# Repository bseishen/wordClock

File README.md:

wordClock
==========

This repository contains my own take on the word clock. Insperation came from an instructable(http://www.instructables.com/id/Sleek-word-clock/). The hardware drives a matrix of 13x8 led's. Uses mosfets for the rows and a TLC5940 for the column driver.

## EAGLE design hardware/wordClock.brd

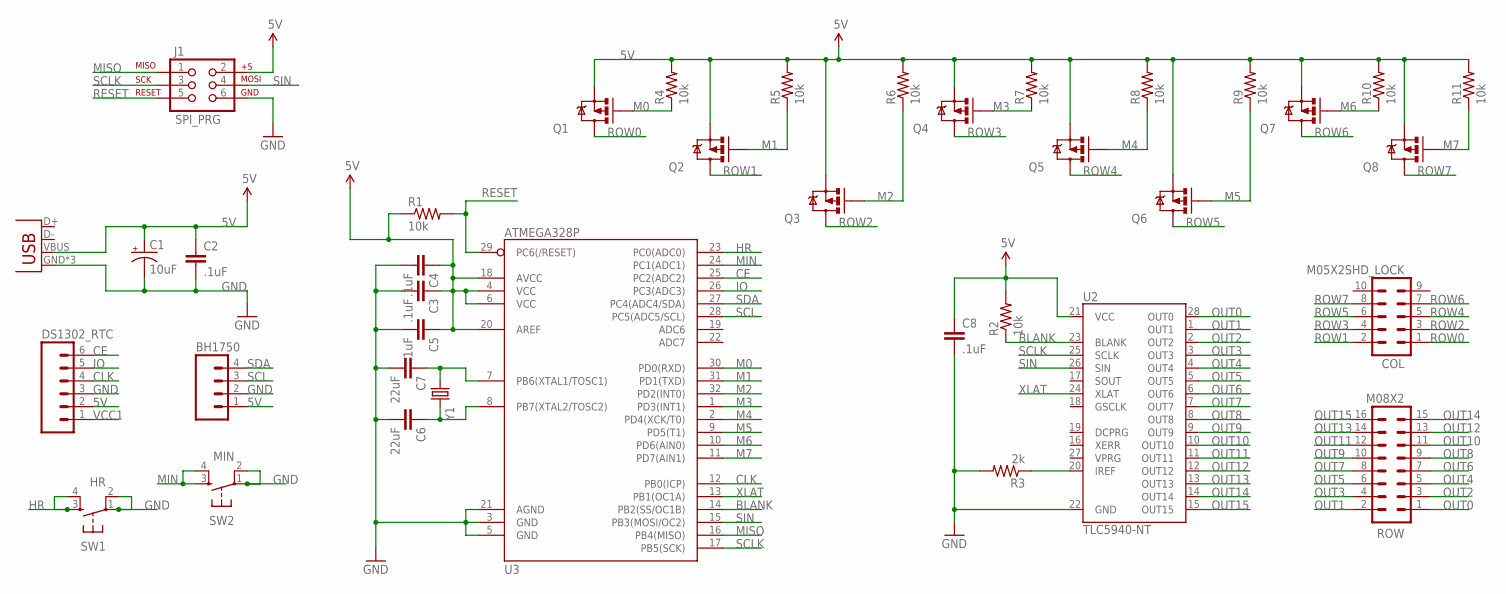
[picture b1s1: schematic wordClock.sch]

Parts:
BH1750: M04LOCK; 1X04_LOCK
C1: 10uF; PANASONIC_D
C2, C3, C4, C5, C8: .1uF; 0805
C6, C7: 22uF; 0805
COL: M05X2SHD_LOCK; 2X5-SHROUDED_LOCK
DS1302_RTC: M06FEMALE_LOCK; 1X06_FEMALE_LOCK.010
J1: SPI_PRG; 2X3_LOCK
JP1: USB-MICROB
Q1, Q2, Q3, Q4, Q5, Q6, Q7, Q8: MOSFET-PCHANNELSMD; SOT23-3
R1, R2, R4, R5, R6, R7, R8, R9, R10, R11: 10k; 0805
R3: 2k; 0805
ROW: M08X2; 2X8
SW1: HR; TACTILE-PTH
SW2: MIN; TACTILE-PTH
U2: TLC5940-NT; DIL28-3
U3: ATMEGA328P; TQFP32-08
Y1: CRYSTALHC49UV; HC49U-V

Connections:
5V: BH1750.1, C1.+, C2.1, C3.1, C4.1, C5.1, C8.1, DS1302_RTC.2, J1.2, JP1.VBUS, Q1.2 (S), Q2.2 (S), Q3.2 (S), Q4.2 (S), Q5.2 (S), Q6.2 (S), Q7.2 (S), Q8.2 (S), R1.1, R2.2, R4.2, R5.2, R6.2, R7.2, R8.2, R9.2, R10.2, R11.2, U2.21 (VCC), U3.4 (VCC), U3.6 (VCC), U3.18 (AVCC), U3.20 (AREF)
BLANK: R2.1, U2.23 (BLANK), U3.14 (PB2(SS/OC1B))
CE: DS1302_RTC.6, U3.25 (PC2(ADC2))
CLK: DS1302_RTC.4, U3.12 (PB0(ICP))
GND: BH1750.2, C1.-, C2.2, C3.2, C4.2, C5.2, C6.2, C7.2, C8.2, DS1302_RTC.3, J1.6, JP1.GND, JP1.MT1 (GND), JP1.MT2 (GND), R3.2, SW1.1, SW1.2, SW2.1, SW2.2, U2.22 (GND), U3.3 (GND), U3.5 (GND), U3.21 (AGND)
HR: SW1.3, SW1.4, U3.23 (PC0(ADC0))
IO: DS1302_RTC.5, U3.26 (PC3(ADC3))
M0: Q1.1 (G), R4.1, U3.30 (PD0(RXD))
M1: Q2.1 (G), R5.1, U3.31 (PD1(TXD))
M2: Q3.1 (G), R6.1, U3.32 (PD2(INT0))
M3: Q4.1 (G), R7.1, U3.1 (PD3(INT1))
M4: Q5.1 (G), R8.1, U3.2 (PD4(XCK/T0))
M5: Q6.1 (G), R9.1, U3.9 (PD5(T1))
M6: Q7.1 (G), R10.1, U3.10 (PD6(AIN0))
M7: Q8.1 (G), R11.1, U3.11 (PD7(AIN1))
MIN: SW2.3, SW2.4, U3.24 (PC1(ADC1))
MISO: J1.1, U3.16 (PB4(MISO))
unnamed: R3.1, U2.20 (IREF)
unnamed: C6.1, U3.8 (PB7(XTAL2/TOSC2)), Y1.2
unnamed: C7.1, U3.7 (PB6(XTAL1/TOSC1)), Y1.1
OUT0: ROW.1, U2.28 (OUT0)
OUT1: ROW.2, U2.1 (OUT1)
OUT2: ROW.3, U2.2 (OUT2)
OUT3: ROW.4, U2.3 (OUT3)
OUT4: ROW.5, U2.4 (OUT4)
OUT5: ROW.6, U2.5 (OUT5)
OUT6: ROW.7, U2.6 (OUT6)
OUT7: ROW.8, U2.7 (OUT7)
OUT8: ROW.9, U2.8 (OUT8)
OUT9: ROW.10, U2.9 (OUT9)
OUT10: ROW.11, U2.10 (OUT10)
OUT11: ROW.12, U2.11 (OUT11)
OUT12: ROW.13, U2.12 (OUT12)
OUT13: ROW.14, U2.13 (OUT13)
OUT14: ROW.15, U2.14 (OUT14)
OUT15: ROW.16, U2.15 (OUT15)
RESET: J1.5, R1.2, U3.29 (PC6(/RESET))
ROW0: COL.1, Q1.3 (D)
ROW1: COL.2, Q2.3 (D)
ROW2: COL.3, Q3.3 (D)
ROW3: COL.4, Q4.3 (D)
ROW4: COL.5, Q5.3 (D)
ROW5: COL.6, Q6.3 (D)
ROW6: COL.7, Q7.3 (D)
ROW7: COL.8, Q8.3 (D)
SCL: BH1750.3, U3.28 (PC5(ADC5/SCL))
SCLK: J1.3, U2.25 (SCLK), U3.17 (PB5(SCK))
SDA: BH1750.4, U3.27 (PC4(ADC4/SDA))
SIN: J1.4, U2.26 (SIN), U3.15 (PB3(MOSI/OC2))
VCC1: DS1302_RTC.1
XLAT: U2.24 (XLAT), U3.13 (PB1(OC1A))

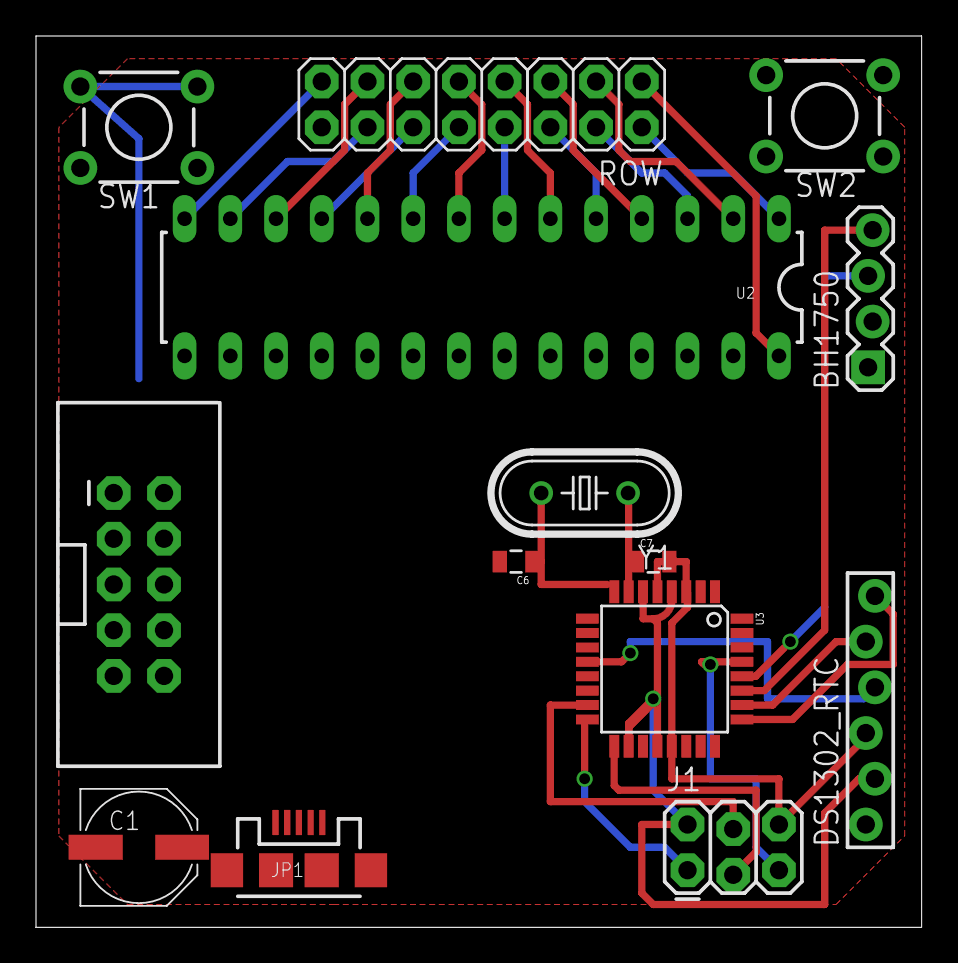
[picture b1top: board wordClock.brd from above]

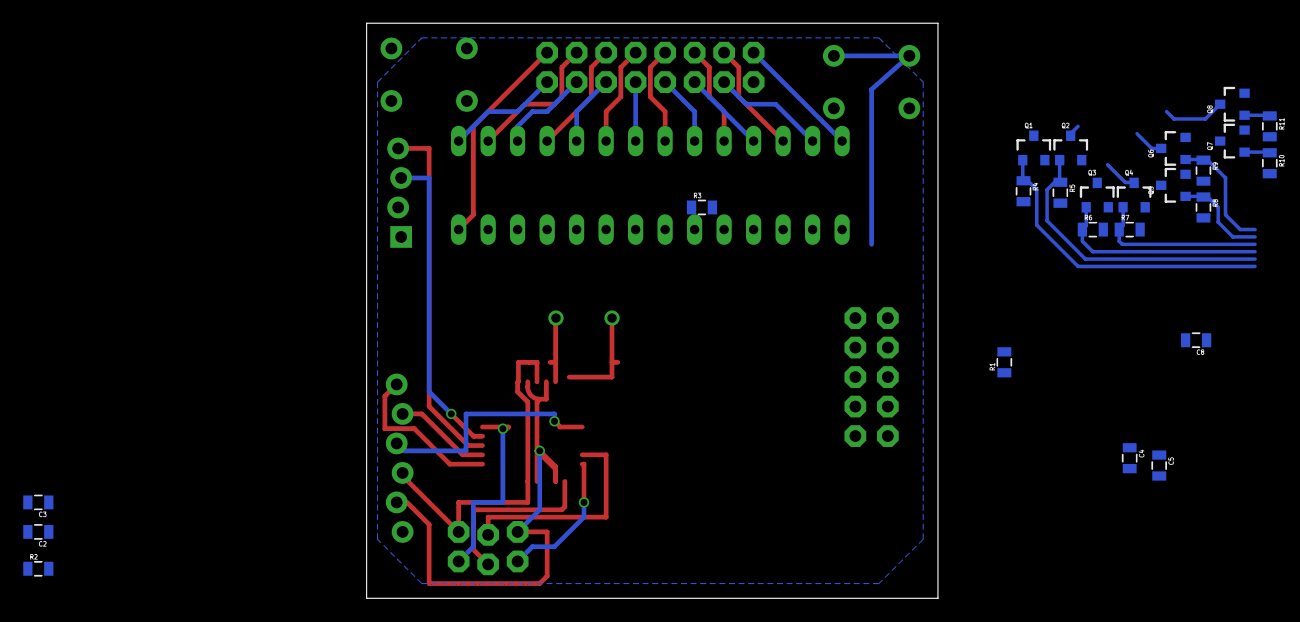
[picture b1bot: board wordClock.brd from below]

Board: 2 copper layers, 49.2 x 49.5 mm, 38 parts (24 on the bottom side), 50 nets.

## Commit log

2013-10-03 Init commit of wordClock schematic.
2013-10-03 added .gitignore, change mosfet layout
    Mosfets now occupy one port, for ease of programming. Mosfet D/S are now
    flipped the right direction.
2013-10-03 Added AVR ISP programming header
2013-10-03 Added readme.md
2013-10-03 Fixed Fet to output pinout added pdf schematic
2013-10-05 updated SPI program socket, atmega, and usb package names to be a little more meaningful
2013-10-05 Added pullup resistors to all P-mosfets
2013-10-05 moved hardware related items in to their own subfolder
2013-10-06 added libraries and dru files
2013-10-06 update changes to atmega component
2013-10-06 uploading progress on board layout and routing
2013-10-08 Fixed floating nets.
    Looks like the atmega got flipped and some nets were left floating.
    Everything should be connected now.
2013-10-08 Fixed ERC errors and Fixed annotation breaks
    Should be all good now, Got broken nets fixed, switched larger usb jack
    for a micro.
2013-10-08 test
2013-10-09 ALL ANNOTATION BREAKS FIXED
2013-10-09 Fixed floating nets
    There was a floating net around the crystal, SCL was named SLI on a pin,
    and various ERC errors fixed.
2013-10-09 Trying my hand at routing the board.
2013-10-14 Updated PDF Schematic
2013-11-05 Flushed V1.0, 1.1 is a complete redesign.
2013-11-05 Version 1.1
    MAJOR BUG, TLC5940NT does't have a GSCLK signal, atmega328 is out of I/O
    pins. New Board Rev. Required.
2013-11-05 Shift Register added to sch
    Since I/O was full on atmega, shift register was added for driving the 8
    mosfets.
2013-11-05 Fixed TLC5940 Missing connections.
    Tied VPRG to GND and DCPRG to VCC.
2013-11-05 Added CNC led board file
    Not finished version.
2013-11-05 Cube issue fix
    changed cube(X,Y,Z) to cube(size = [x,y,z])
2013-11-05 organized models into src and output with an automatic make file to export all of the source files
2013-11-05 improved rendering of LEDBoard by unconstraining the generation of the board and making the spacing of the cavities dynamic based on a desired number of cols and rows
2013-11-05 updated rendering of stl files from src
2013-11-08 Added DXF output of light boxes and aligned svg
    SVG is now aligned with the lightboxes.
2013-11-08 Recompiled STL
2013-11-08 Recompiled again.

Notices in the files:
parts and their libraries:
SparkFun-Connectors: Licensing: CC v3.0 Share-Alike You are welcome to use this library for commercial purposes.
